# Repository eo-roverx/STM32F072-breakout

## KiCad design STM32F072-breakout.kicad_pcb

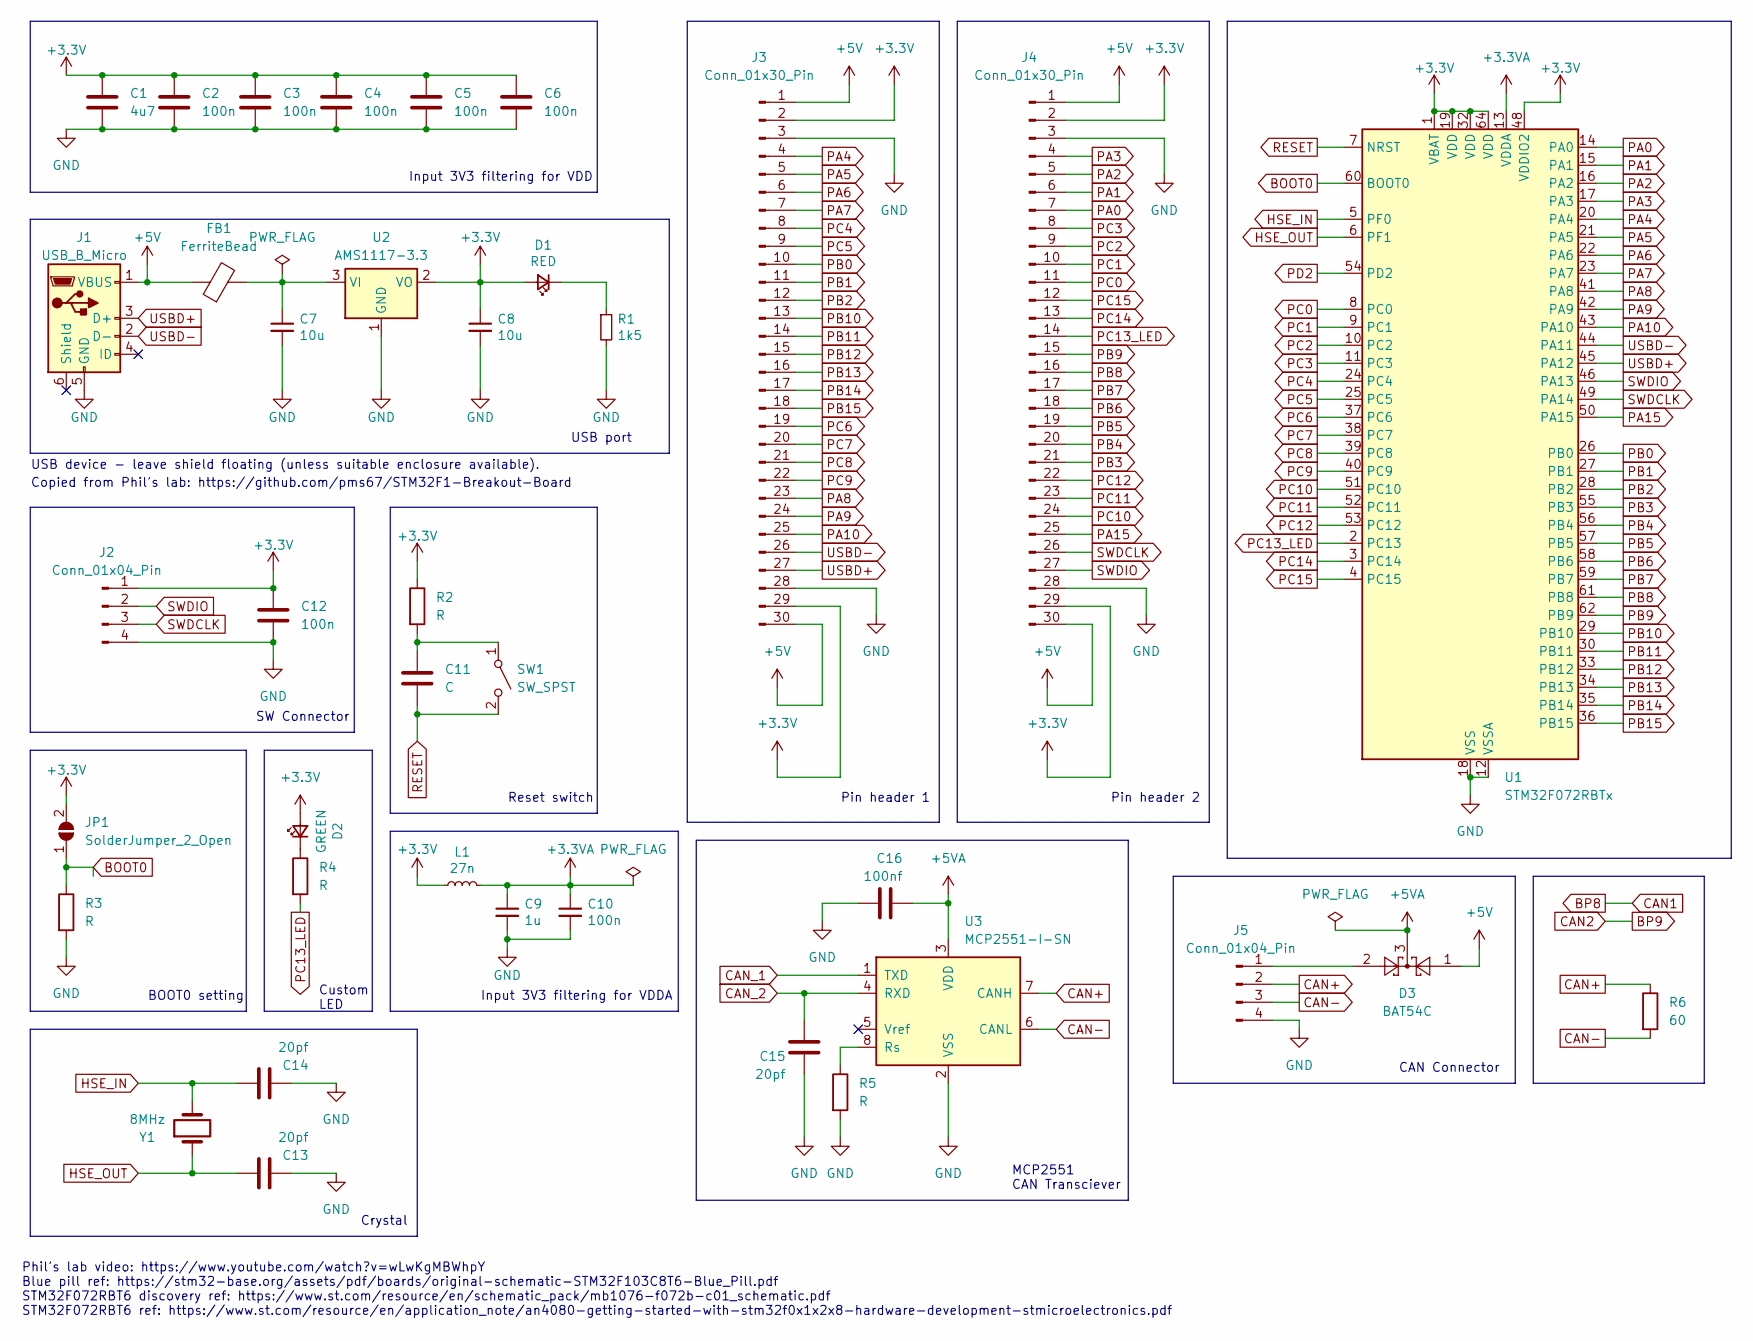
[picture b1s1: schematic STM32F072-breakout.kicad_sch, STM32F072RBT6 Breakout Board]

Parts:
C1: 4u7; C_0805_2012Metric
C2, C3, C4, C5, C6, C12: 100n; C_0805_2012Metric
C7, C8: 10u; C_0603_1608Metric; LCSC Part # C15849
C9: 1u; C_0402_1005Metric; LCSC Part # C52923
C10: 100n; C_0402_1005Metric; LCSC Part # C1525
C11: C; C_0603_1608Metric
C13, C14, C15: 20pf; C_0603_1608Metric
C16: 100nf; C_0603_1608Metric
D1: RED; LED_0603_1608Metric; LCSC Part # C72043
D2: GREEN; LED_0603_1608Metric; LCSC Part # C72043
D3: BAT54C; SOT-23
FB1: FerriteBead; L_0805_2012Metric
J1: USB_B_Micro; USB_Micro-B_Wuerth_629105150521
J2: Conn_01x04_Pin; PinHeader_1x04_P1.00mm_Horizontal
J3, J4: Conn_01x30_Pin; PinHeader_1x30_P1.00mm_Vertical
J5: Conn_01x04_Pin; PinHeader_1x04_P1.00mm_Vertical
JP1: SolderJumper_2_Open; SolderJumper-2_P1.3mm_Open_Pad1.0x1.5mm
L1: 27n; L_0402_1005Metric; LCSC Part # C18830
R1: 1k5; R_0603_1608Metric; LCSC Part # C22843
R2, R5: R; R_0805_2012Metric
R3, R4: R; R_0603_1608Metric
R6: 60; R_0805_2012Metric
SW1: SW_SPST; SW_SPST_EVQPE1
U1: STM32F072RBTx; LQFP-64_10x10mm_P0.5mm
U2: AMS1117-3.3; SOT-223-3_TabPin2
U3: MCP2551-I-SN; SOIC-8_3.9x4.9mm_P1.27mm
Y1: 8MHz; Crystal_SMD_0603-2Pin_6.0x3.5mm

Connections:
+3.3V: C1.1, C2.1, C3.1, C4.1, C5.1, C6.1, C8.1, C12.1, D1.2 (A), D2.2 (A), J2.1, J3.2, J3.29, J4.2, J4.29, JP1.2 (B), L1.1, R2.1, U1.1 (VBAT), U1.19 (VDD), U1.32 (VDD), U1.48 (VDDIO2), U1.64 (VDD), U2.2 (VO)
+3.3VA: C9.1, C10.1, L1.2, U1.13 (VDDA)
+5V: D3.1, FB1.1, J1.1 (VBUS), J3.1, J3.30, J4.1, J4.30
+5VA: C16.2, D3.3, U3.3 (VDD)
BOOT0: JP1.1 (A), R3.1, U1.60 (BOOT0)
CAN+: J5.2, R6.1, U3.7 (CANH)
CAN-: J5.3, R6.2, U3.6 (CANL)
CAN_1: U3.1 (TXD)
CAN_2: C15.2, U3.4 (RXD)
GND: C1.2, C2.2, C3.2, C4.2, C5.2, C6.2, C7.2, C8.2, C9.2, C10.2, C12.2, C13.2, C14.2, C15.1, C16.1, J1.5 (GND), J2.4, J3.3, J3.28, J4.3, J4.28, J5.4, R1.2, R3.2, R5.2, U1.12 (VSSA), U1.18 (VSS), U1.31 (VSS), U1.47 (VSS), U1.63 (VSS), U2.1 (GND), U3.2 (VSS)
HSE_IN: C14.1, U1.5 (PF0), Y1.2
HSE_OUT: C13.1, U1.6 (PF1), Y1.1
unnamed: D1.1 (K), R1.1
unnamed: D2.1 (K), R4.1
unnamed: D3.2, J5.1
unnamed: C11.1, R2.2, SW1.1 (A)
unnamed: C7.1, FB1.2, U2.3 (VI)
unnamed: R5.1, U3.8 (Rs)
PA0: J4.7, U1.14 (PA0)
PA1: J4.6, U1.15 (PA1)
PA2: J4.5, U1.16 (PA2)
PA3: J4.4, U1.17 (PA3)
PA4: J3.4, U1.20 (PA4)
PA5: J3.5, U1.21 (PA5)
PA6: J3.6, U1.22 (PA6)
PA7: J3.7, U1.23 (PA7)
PA8: J3.23, U1.41 (PA8)
PA9: J3.24, U1.42 (PA9)
PA10: J3.25, U1.43 (PA10)
PA15: J4.25, U1.50 (PA15)
PB0: J3.10, U1.26 (PB0)
PB1: J3.11, U1.27 (PB1)
PB2: J3.12, U1.28 (PB2)
PB3: J4.21, U1.55 (PB3)
PB4: J4.20, U1.56 (PB4)
PB5: J4.19, U1.57 (PB5)
PB6: J4.18, U1.58 (PB6)
PB7: J4.17, U1.59 (PB7)
PB8: J4.16, U1.61 (PB8)
PB9: J4.15, U1.62 (PB9)
PB10: J3.13, U1.29 (PB10)
PB11: J3.14, U1.30 (PB11)
PB12: J3.15, U1.33 (PB12)
PB13: J3.16, U1.34 (PB13)
PB14: J3.17, U1.35 (PB14)
PB15: J3.18, U1.36 (PB15)
PC0: J4.11, U1.8 (PC0)
PC1: J4.10, U1.9 (PC1)
PC2: J4.9, U1.10 (PC2)
PC3: J4.8, U1.11 (PC3)
PC4: J3.8, U1.24 (PC4)
PC5: J3.9, U1.25 (PC5)
PC6: J3.19, U1.37 (PC6)
PC7: J3.20, U1.38 (PC7)
PC8: J3.21, U1.39 (PC8)
PC9: J3.22, U1.40 (PC9)
PC10: J4.24, U1.51 (PC10)
PC11: J4.23, U1.52 (PC11)
PC12: J4.22, U1.53 (PC12)
PC13_LED: J4.14, R4.2, U1.2 (PC13)
PC14: J4.13, U1.3 (PC14)
PC15: J4.12, U1.4 (PC15)
PD2: U1.54 (PD2)
RESET: C11.2, SW1.2 (B), U1.7 (NRST)
SWDCLK: J2.3, J4.26, U1.49 (PA14)
SWDIO: J2.2, J4.27, U1.46 (PA13)
USBD+: J1.3 (D+), J3.27, U1.45 (PA12)
USBD-: J1.2 (D-), J3.26, U1.44 (PA11)

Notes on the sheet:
CAN Connector
USB device - leave shield floating (unless suitable enclosure available).
Pin header 2
USB port
SW Connector
BOOT0 setting
Pin header 1
Input 3V3 filtering for VDD
Reset switch
Custom LED
Crystal
Phil's lab video: https://www.youtube.com/watch?v=wLwKgMBWhpY Blue pill ref: https://stm32-base.org/assets/pdf/boards/original-schematic-STM32F103C8T6-Blue_Pill.pdf STM32F072RBT6 discovery ref: https://www.st.com/resource/en/schematic_pack/mb1076-f072b-c01_schematic.pdf STM32F072RBT6 ref: https://w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
Copied from Phil's lab: https://github.com/pms67/STM32F1-Breakout-Board
Input 3V3 filtering for VDDA
MCP2551 CAN Transciever

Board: 2 copper layers, 38 parts (0 on the bottom side), 66 nets, no tracks yet.

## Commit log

2023-10-22 add one more header
2023-10-22 add user LED
2023-10-22 make same size headers
2023-10-22 reroute headers
2023-10-22 add CAN MCP2551
2023-10-22 use ams1117 for 3.3V
2023-10-22 fix missing CAN connection
